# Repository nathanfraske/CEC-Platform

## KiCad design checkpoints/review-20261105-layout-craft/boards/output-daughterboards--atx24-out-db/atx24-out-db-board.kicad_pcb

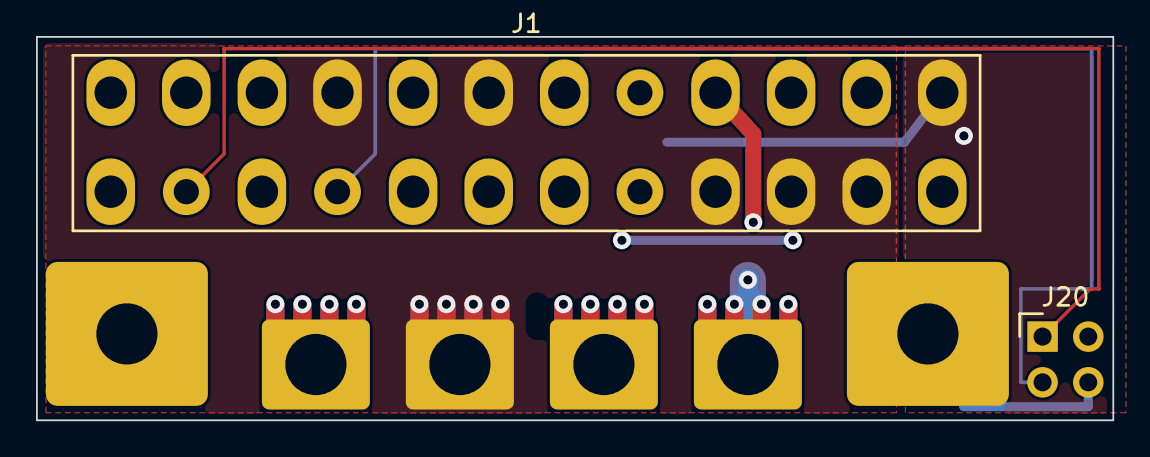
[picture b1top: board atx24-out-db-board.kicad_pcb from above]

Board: 4 copper layers, 59.8 x 21.3 mm, 8 parts (0 on the bottom side), 8 nets.

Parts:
J1: ATX24 OUT FIELD; ATX24_Daughterboard_Field_P4.20mm
J10, J11, J13, J15: T34069 DB M3 PAD; XFCN_T34069_Daughterboard_BoltPad_M3_PROVISIONAL
J16, J19: TTR32100127-0600 DB M3 PAD; XFCN_TTR32100127-0600_Daughterboard_BoltPad_M3_PROVISIONAL
J20: TSW-102-16-G-D-RA; Samtec_TSW-102-16-G-D-RA_2x02_P2.54mm_Horizontal

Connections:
+3V3: J1.1, J1.2, J1.12, J1.13, J13.1
+5V: J1.4, J1.6, J1.21, J1.22, J1.23, J11.1
+5VSB: J1.9, J15.1
+12V: J1.10, J1.11, J10.1
/-12V: J1.14, J20.1
/PS_ON#: J1.16, J20.2
/PWR_OK: J1.8, J20.3
GND: J1.3, J1.5, J1.7, J1.15, J1.17, J1.18, J1.19, J1.24, J16.1, J19.1, J20.4

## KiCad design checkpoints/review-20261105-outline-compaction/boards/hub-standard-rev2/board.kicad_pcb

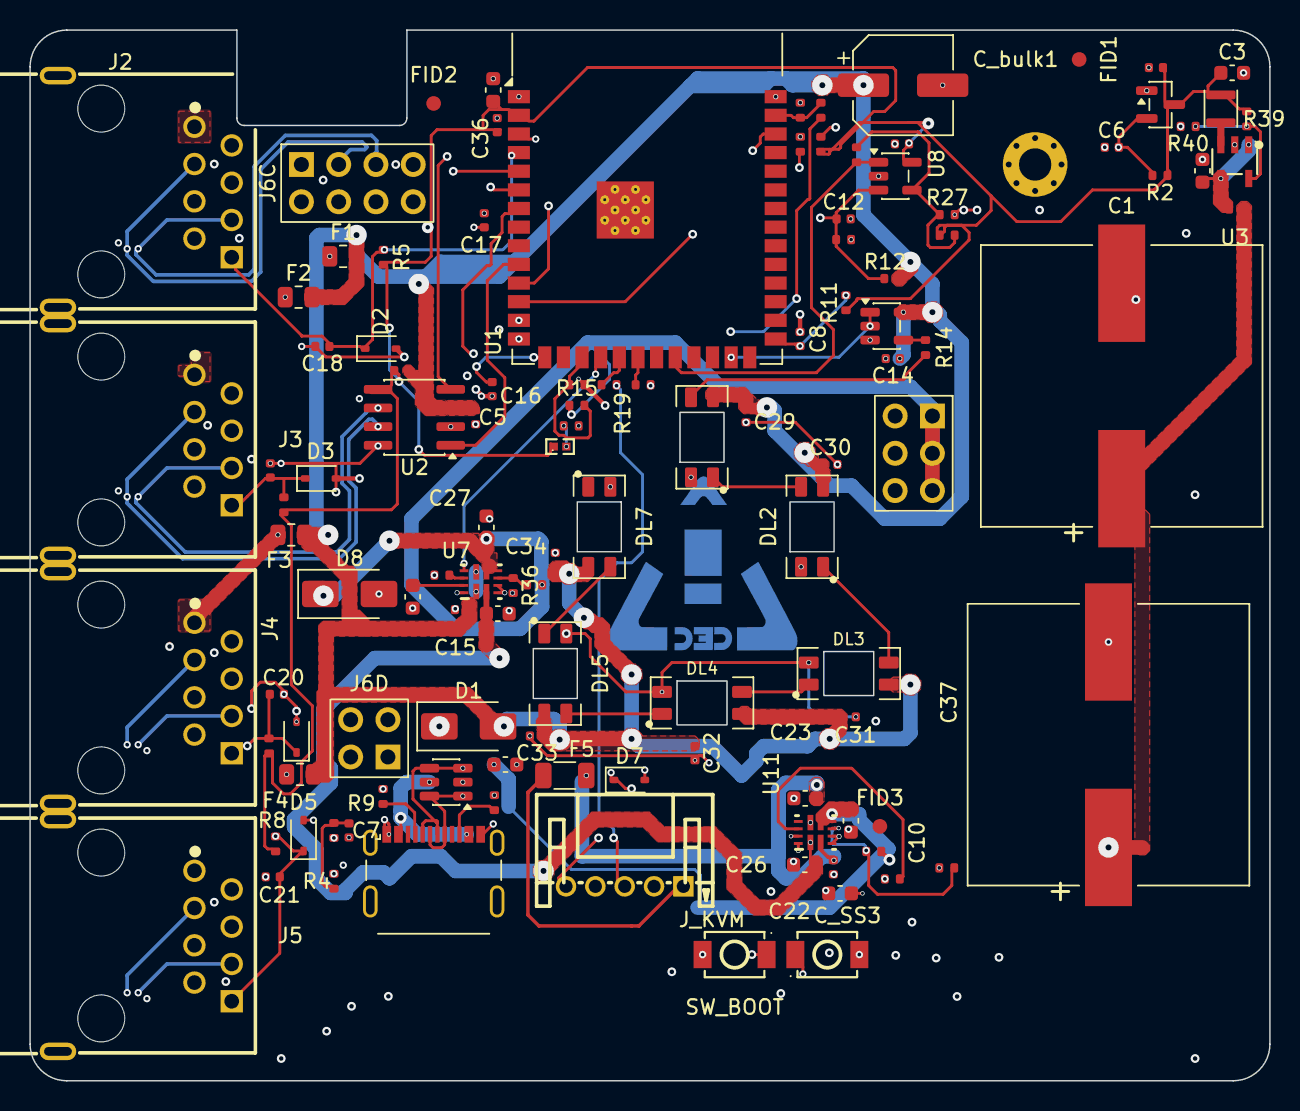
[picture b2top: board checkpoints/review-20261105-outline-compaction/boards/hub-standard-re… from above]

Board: 6 copper layers, 84.5 x 71.6 mm, 117 parts (1 on the bottom side), 58 nets.

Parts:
C1, C37: 4700uF; CP_Elec_Lelon_VZH_18x16.5
C2, C3, C23: 10uF; C_0603_1608Metric
C4, C5, C6, C8, C13, C14, C15, C16, C17, C18, C19, C20, C21, C22, C29, C30, C31, C32, C33, C34, C35, C36: 100nF; C_0402_1005Metric
C7: 4n7; C_0402_1005Metric
C10, C25, C26, C27, C28: 1uF; C_0603_1608Metric
C11: 22uF; C_0603_1608Metric
C12: 10nF; C_0402_1005Metric
C_SS2, C_SS3: 2.2uF; C_0603_1608Metric
C_bulk1: 470uF; CP_Elec_6.3x7.7
D1: SS14; D_SMA
D2, D3, D4, D5, D7: PESD5V0S1BA; D_SOD-323
D6: USBLC6-2SC6; SOT-23-6
D8: SMAJ5.0A; D_SMA
DL1, DL2, DL3, DL4, DL5, DL7: SK6812MINI-E; LED_SK6812MINI-E_3.2x2.8mm_P1.5mm_ReverseMount
F1, F2, F3, F4: PTC 500mA; R_0805_2012Metric
F5: 1.1A/16V PTC; R_1206_3216Metric
FID1, FID2, FID3: Fiducial_1mm_Mask2mm
H1: M2 GND lug; MountingHole_2.2mm_M2_Pad_Via_Slim_6mm_Hardware
J2: PORT1; RJ45_FTP_Shielded_Horizontal
J3: PORT2; RJ45_FTP_Shielded_Horizontal
J4: PORT3; RJ45_FTP_Shielded_Horizontal
J5: PORT4; RJ45_FTP_Shielded_Horizontal
J6C: TO-24PIN-STACK-COMMS; PinSocket_2x04_P2.54mm_Vertical
J6D: TO-24PIN-STACK-ID; PinSocket_2x02_P2.54mm_Vertical
J6P: TO-24PIN-STACK-PWR; PinSocket_2x03_P2.54mm_Vertical
J_KVM: CEC_NANOKVM_AUX_5P; JST_PH_S5B-PH-K-S_1x05_P2.00mm_Horizontal
J_USB: USB-C; USB_C_Receptacle_GCT_USB4215-03-A
L1: 2.2uH; VLS252010HBX-2R2M-1
LOGO1: CEC_Logo_Copper
R2, R5, R6, R7, R8, R11, R16, R22, R24, R25, R36, R38: 10kΩ; R_0402_1005Metric
R3, R4: 60.4; R_0402_1005Metric
R9, R10: 5.1kΩ; R_0402_1005Metric
R12, R15, R21, R23: 47kΩ; R_0402_1005Metric
R13: 27kΩ; R_0402_1005Metric
R14: 330Ω; R_0402_1005Metric
R19, R20: 33Ω; R_0402_1005Metric
R26: 11.0kOhm; R_0402_1005Metric
R27: 10.0kOhm; R_0402_1005Metric
R28: 1MOhm; R_0402_1005Metric
R35, R37: 43.2kΩ; R_0402_1005Metric
R39: 453kΩ; R_0402_1005Metric
R40: 100kΩ; R_0402_1005Metric
RJ_HOLD: 0R (jumper); R_0402_1005Metric
R_ILIM2, R_ILIM3: 27kΩ; R_0402_1005Metric
SW_BOOT: SW_BOOT; TS-1088-AR02016
SW_RESET: SW_RST; TS-1088-AR02016
TH1: NTC 10k; NTC_0402_1005Metric
U1: ESP32-S3-WROOM-1; ESP32-S3-WROOM-1_NoAntKeepout
U2: TJA1051T/3; SOIC-8_3.9x4.9mm_P1.27mm
U3: TLV62569DBVR; SOT-23-5_L3.0-W1.7-P0.95-LS2.8-BL
U4: TPS3839K33; SOT-23
U6: SN74AHCT1G08; SOT-23-5
U7, U11: TPS2121RUXR; RUX0012A
U8: TLV7011DBVR; SOT-23-5

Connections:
+3V3: C3.1, C4.1, C11.1, C13.1, C17.1, C35.1, C36.1, L1.2, R2.1, R5.1, R6.1, R7.1, R8.1, R11.1, R23.1, R26.1, R39.1, TH1.1, U1.2, U2.5, U4.3, U8.5
+5VSB: C5.1, C14.1, C15.1, C29.1, C30.1, C31.1, C32.1, C33.1, C34.1, C35.2, C_bulk1.1, D1.2, DL1.4, DL2.4, DL3.4, DL4.4, DL5.4, DL7.4, F1.2, F2.2, F3.2, F4.2, R12.1, U2.3, U6.5, U7.1, U7.8
+5V_SYS: C27.1, D8.1, J6P.1, J6P.3, J6P.5, R15.1, R35.1, U7.6, U7.7
/5V_SYS_SENSE: R15.2, R16.1, U1.17
/AUX_UART_RX: R20.1, U1.20
/AUX_UART_TX: R19.1, U1.19
/BLACKOUT_SENSE: C12.1, R12.2, R13.1, U1.12, U8.3
/CAN + FOUR MODULE PORTS + STACK/CAN_H: J2.3, J3.3, J4.3, J5.3, J6C.3, R3.1, U2.7
/CAN + FOUR MODULE PORTS + STACK/CAN_L: J2.6, J3.6, J4.6, J5.6, J6C.5, R4.2, U2.6
/CAN + FOUR MODULE PORTS + STACK/CAN_MID: C7.1, R3.2, R4.1
/CAN + FOUR MODULE PORTS + STACK/VCC_P1: F1.1, J2.1
/CAN + FOUR MODULE PORTS + STACK/VCC_P2: F2.1, J3.1
/CAN + FOUR MODULE PORTS + STACK/VCC_P3: F3.1, J4.1
/CAN + FOUR MODULE PORTS + STACK/VCC_P4: F4.1, J5.1
/CAN_RX: U1.11, U2.4
/CAN_TX: U1.10, U2.1
/DETECT1: C18.1, D2.1, J2.8, J6D.1, R5.2, U1.4
/DETECT2: C19.1, D3.1, J3.8, R6.2, U1.5
/DETECT3: C20.1, D4.1, J4.8, R7.2, U1.6
/DETECT4: C21.1, D5.1, J5.8, R8.2, U1.7
/HOLD-UP + 3V3 REGULATOR/+5V_HOLD: C1.1, C37.1, D1.1, RJ_HOLD.1
/HOLD-UP + 3V3 REGULATOR/BUCK_FB_3V3: R39.2, R40.1, U3.5
/HOLD-UP + 3V3 REGULATOR/BUCK_SW_3V3: L1.1, U3.3
/HOLD-UP + 3V3 REGULATOR/COMP_THRESH: R26.2, R27.1, R28.2, U8.4
/HOLD-UP + 3V3 REGULATOR/LOGIC_REG_IN: C2.1, RJ_HOLD.2, U3.1, U3.4
/HUB_3V3_SENSE: R23.2, R24.1, U1.38
/KVM AUXILIARY + RAIL SENSING/AUX_RXC: J_KVM.4, R20.2
/KVM AUXILIARY + RAIL SENSING/AUX_TXC: J_KVM.3, R19.2
/KVM AUXILIARY + RAIL SENSING/KVM_3V3_REF: D7.1, J_KVM.5, R21.1
/KVM AUXILIARY + RAIL SENSING/KVM_5V_RAW: F5.1, J_KVM.1
/KVM_3V3_SENSE: R21.2, R22.1, U1.39
/KVM_5V_IN: C22.1, C23.1, F5.2, U11.2
/LED_DATA: U1.25, U6.1, U6.2
/MCU + USB SERVICE PORT/EN: C6.2, R2.2, SW_RESET.2, U1.3, U4.2
/MCU + USB SERVICE PORT/GPIO0: C8.1, R11.2, SW_BOOT.2, U1.27
/MCU + USB SERVICE PORT/USB_CC1: J_USB.A5, R9.1
/MCU + USB SERVICE PORT/USB_CC2: J_USB.B5, R10.1
/MCU + USB SERVICE PORT/USB_D_N: D6.3, D6.4, J_USB.A7, J_USB.B7, U1.13
/MCU + USB SERVICE PORT/USB_D_P: D6.1, D6.6, J_USB.A6, J_USB.B6, U1.14
/POWER INPUT + SOURCE SELECTION/PSU_5V_KVM: C26.1, C28.1, U7.2, U11.1, U11.8
/POWER INPUT + SOURCE SELECTION/U7_ILM: R_ILIM2.1, U7.10
/POWER INPUT + SOURCE SELECTION/U7_OV1: R35.2, R36.1, U7.5
/POWER INPUT + SOURCE SELECTION/U7_SS: C_SS2.1, U7.11
/POWER INPUT + SOURCE SELECTION/U11_ILM: R_ILIM3.1, U11.10
/POWER INPUT + SOURCE SELECTION/U11_OV1: R37.2, R38.1, U11.5
/POWER INPUT + SOURCE SELECTION/U11_SS: C_SS3.2, U11.11
/PWR_FAIL_INT: R28.1, U1.22, U8.1
/PWR_SOURCE_STATUS: U1.18, U7.9
/STATUS LED CHAIN/Net-(U6-Y): R14.1, U6.4
/TEMP_HUB: C16.1, R25.1, TH1.2, U1.15
/USB_VBUS: C10.1, C25.1, D6.5, J_USB.A4, J_USB.A9, J_USB.B4, J_USB.B9, R37.1, U11.6, U11.7
GND: C1.2, C2.2, C3.2, C4.2, C5.2, C6.1, C7.2, C8.2, C10.2, C11.2, C12.2, C13.2, C14.2, C15.2, C16.2, C17.2, C18.2, C19.2, C20.2, C21.2, C22.2, C23.2, C25.2, C26.2, C27.2, C28.2, C29.2, C30.2, C31.2, C32.2, C33.2, C34.2, C36.2, C37.2, C_SS2.2, C_SS3.1, C_bulk1.2, D2.2, D3.2, D4.2, D5.2, D6.2, D7.2, D8.2, DL1.2, DL2.2, DL3.2, DL4.2, DL5.2, DL7.2, H1.1, J2.2, J2.SH1, J2.SH2, J3.2, J3.SH1, J3.SH2, J4.2, J4.SH1, J4.SH2, J5.2, J5.SH1, J5.SH2, J6C.1, J6C.2, J6C.7, J6C.8, J6D.2, J6D.4, J6P.2, J6P.4, J6P.6, J_KVM.2, J_USB.A1, J_USB.A12, J_USB.B1, J_USB.B12, J_USB.S1, R9.2, R10.2, R13.2, R16.2, R22.2, R24.2, R25.2, R27.2, R36.2, R38.2, R40.2, R_ILIM2.2, R_ILIM3.2, SW_BOOT.1, SW_RESET.1, U1.1, U1.40, U1.41, U2.2, U2.8, U3.2, U4.1, U6.3, U7.3, U7.4, U7.12, U8.2, U11.3, U11.4, U11.12
unnamed: DL1.3, R14.2
unnamed: DL1.1, DL2.3
unnamed: DL2.1, DL3.3
unnamed: DL3.1, DL4.3
unnamed: DL4.1, DL5.3
unnamed: DL5.1, DL7.3

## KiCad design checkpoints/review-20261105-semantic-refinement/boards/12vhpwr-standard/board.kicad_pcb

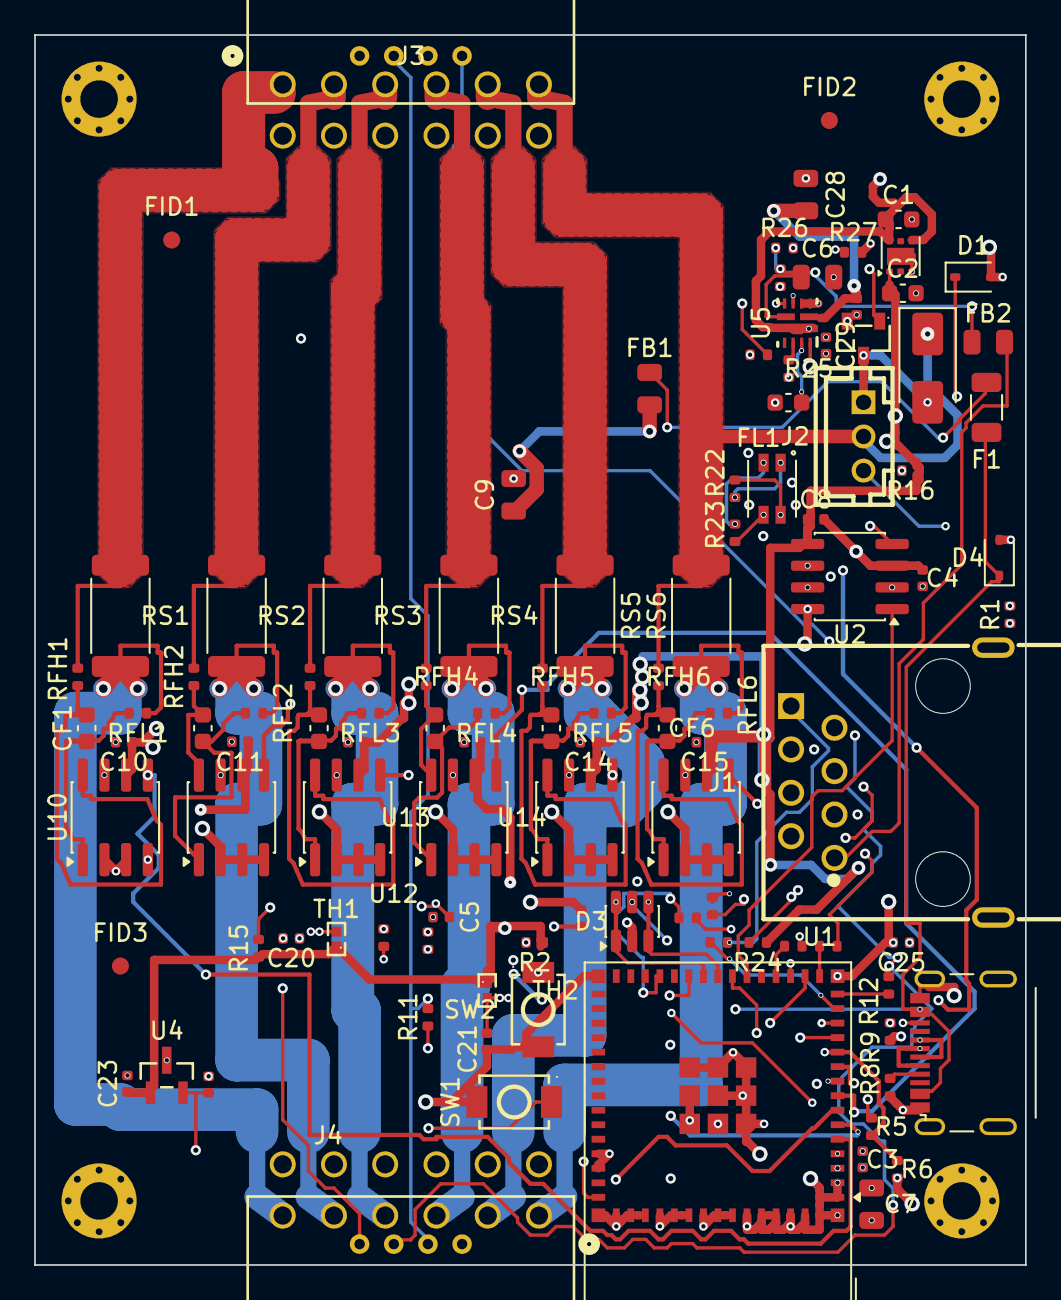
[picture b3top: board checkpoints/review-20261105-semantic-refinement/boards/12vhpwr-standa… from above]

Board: 6 copper layers, 58.0 x 72.0 mm, 110 parts (0 on the bottom side), 73 nets.

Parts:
C1: 10uF; C_0603_1608Metric
C2: 1uF; C_0603_1608Metric
C3, C4, C5, C8, C10, C11, C12, C13, C14, C15, C20, C21, C22, C23, C25, C27, C29: 100nF; C_0402_1005Metric
C6, C7, C9, C28: 10uF; C_0805_2012Metric
C24: 1nF; C_0402_1005Metric
C26: 2.2uF; C_0603_1608Metric
CF1, CF2, CF3, CF4, CF5, CF6: 470nF; C_0603_1608Metric
D1, D4: PESD5V0S1BA; D_SOD-323
D3: USBLC6-2SC6; SOT-23-6
D5: SS34; D_SMA
F1: 750mA/16V PTC; R_1206_3216Metric
FB1: MPZ2012S601AT000; C_0805_2012Metric
FB2: 0R; C_0805_2012Metric
FID1, FID2, FID3: Fiducial_1mm_Mask2mm
FL1: ACT1210L-101-2P-TL00 (DNP); TDK_ACT1210L_CEC_13_24
H1, H2, H3, H4: M2_PTH_GND_Slim_6mm_Hardware; MountingHole_2.2mm_M2_Pad_Via_Slim_6mm_Hardware
J1: TO-HUB; RJ45_FTP_Shielded_Horizontal
J2: CEC_FAN_3P; JST_PH_B3B-PH-K-S_1x03_P2.00mm_Vertical
J3: 12V-2x6 IN; CEC_12V2x6_Horizontal
J4: 12V-2x6 OUT pigtail; CEC_12V2x6_Horizontal
J5: USB-C 2.0; USB_C_Receptacle_GCT_USB4215-03-A
Q1: AO3400A; SOT-23-3_L2.9-W1.3-P1.90-LS2.4-BR
R1: 2.2kΩ; R_0402_1005Metric
R2, R6, R15, R16, R20, R21, R24, R27: 10kΩ; R_0402_1005Metric
R5: 47kΩ; R_0402_1005Metric
R7, R25, R28: 100kΩ; R_0402_1005Metric
R8, R9: 5.1kΩ; R_0402_1005Metric
R10, R11, R12, R13, R17: 1kΩ; R_0402_1005Metric
R14: 100Ω; R_0402_1005Metric
R22, R23: 0Ω; R_0402_1005Metric
R26: 43.2kΩ; R_0402_1005Metric
R29: 33kΩ; R_0402_1005Metric
RFH1, RFH2, RFH3, RFH4, RFH5, RFH6: 10Ω; R_0402_1005Metric
RFL1, RFL2, RFL3, RFL4, RFL5, RFL6: 10Ω; R_0402_1005Metric
RS1, RS2, RS3, RS4, RS5, RS6: 1mΩ; R_2512_6332Metric
SW1: BOOT; TS-1088-AR02016
SW2: RESET; TS-1088-AR02016
TH1, TH2: NTC 10k; NTC_0402_1005Metric
U1: ESP32-S3-MINI-1-N4R2; ESP32-S2-MINI-1_NoAntKeepout
U2: TJA1051T/3; SOIC-8_3.9x4.9mm_P1.27mm
U4: REF3030; REF3030_DBZ3
U5: TPS2121RUXR; RUX0012A
U10, U11, U12, U13, U14, U15: INA240A3; SOIC-8_3.9x4.9mm_P1.27mm
U16: TLV75533PDRVR; WSON-6-1EP_2x2mm_P0.65mm_EP1x1.6mm

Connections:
+3V3: C2.1, C3.1, C7.1, C8.1, C10.1, C11.1, C12.1, C13.1, C14.1, C15.1, C23.1, R2.1, R15.1, R16.1, R24.1, TH1.1, TH2.1, U1.3, U2.5, U4.1, U10.6, U11.6, U12.6, U13.6, U14.6, U15.6, U16.1
+5VSB: C1.1, C4.1, C8.2, C29.1, U2.3, U5.1, U5.8, U16.4, U16.6
/01-input/FAN_GATE: Q1.1, R14.2, R15.2
/01-input/FAN_RET: D5.2, J2.1, Q1.3
/01-input/FAN_TACH: J2.3, R16.2, R17.1
/08-usb/U5_ILM: R25.1, U5.10
/08-usb/U5_OV1: R26.2, R27.1, U5.5
/08-usb/U5_PR1: R28.2, R29.1, U5.6
/08-usb/U5_SS: C26.1, U5.11
/CAN_H: FL1.1, J1.3, R22.1
/CAN_H_INT: FL1.3, R22.2, U2.7
/CAN_L: FL1.2, J1.6, R23.1
/CAN_L_INT: FL1.4, R23.2, U2.6
/CAN_RX: U1.22, U2.4
/CAN_TX: U1.21, U2.1
/DETECT: D1.1, J1.8, R1.1, R7.1
/DETECT_SENSE: R7.2, U1.14
/EN: C5.1, R2.2, SW2.2, U1.45
/FAN_12V: D5.1, J2.2, J3.6, R5.1, RFH6.1, RS6.1
/FAN_EN: R14.1, U1.25
/FAN_TACH_GPIO: R17.2, U1.27
/GPIO0: C25.1, R24.2, SW1.2, U1.4
/IN1_N: CF1.2, RFL1.2, U10.1
/IN1_P: CF1.1, RFH1.2, U10.8
/IN2_N: CF2.2, RFL2.2, U11.1
/IN2_P: CF2.1, RFH2.2, U11.8
/IN3_N: CF3.2, RFL3.2, U12.1
/IN3_P: CF3.1, RFH3.2, U12.8
/IN4_N: CF4.2, RFL4.2, U13.1
/IN4_P: CF4.1, RFH4.2, U13.8
/IN5_N: CF5.2, RFL5.2, U14.1
/IN5_P: CF5.1, RFH5.2, U14.8
/IN6_N: CF6.2, RFL6.2, U15.1
/IN6_P: CF6.1, RFH6.2, U15.8
/ISENSEP1: U1.5, U10.5
/ISENSEP2: U1.6, U11.5
/ISENSEP3: U1.7, U12.5
/ISENSEP4: U1.8, U13.5
/ISENSEP5: U1.9, U14.5
/ISENSEP6: U1.10, U15.5
/SB_CBL_PRES: J3.16, J4.16, R13.1
/SB_CBL_PRES_GPIO: R13.2, U1.16
/SB_PWR_STABLE: J3.15, J4.15, R12.1
/SB_PWR_STABLE_GPIO: R12.2, U1.15
/SB_SENSE0: J3.13, J4.13, R10.1
/SB_SENSE0_GPIO: R10.2, U1.19
/SB_SENSE1: J3.14, J4.14, R11.1
/SB_SENSE1_GPIO: R11.2, U1.13
/SENSEP1_HI: J3.1, RFH1.1, RS1.1
/SENSEP1_LO: J4.6, RFL1.1, RS1.2
/SENSEP2_HI: J3.2, RFH2.1, RS2.1
/SENSEP2_LO: J4.5, RFL2.1, RS2.2
/SENSEP3_HI: J3.3, RFH3.1, RS3.1
/SENSEP3_LO: J4.4, RFL3.1, RS3.2
/SENSEP4_HI: J3.4, RFH4.1, RS4.1
/SENSEP4_LO: J4.3, RFL4.1, RS4.2
/SENSEP5_HI: J3.5, RFH5.1, RS5.1
/SENSEP5_LO: J4.2, RFL5.1, RS5.2
/SENSEP6_LO: J4.1, RFL6.1, RS6.2
/TEMP1: C20.1, R20.1, TH1.2, U1.17
/TEMP2: C21.1, R21.1, TH2.2, U1.18
/USB_CC1: J5.A5, R8.1
/USB_CC2: J5.B5, R9.1
/USB_DM: D3.3, D3.4, J5.A7, J5.B7, U1.23
/USB_DP: D3.1, D3.6, J5.A6, J5.B6, U1.24
/VBUS: C9.1, C27.1, C28.1, FB1.2, U5.2
/VBUS_F: F1.2, FB1.1
/VBUS_RAW: D3.5, D4.1, F1.1, J5.A4, J5.A9, J5.B4, J5.B9
/VCC_RAW: FB2.2, J1.1
/VCC_RJ45: C6.1, FB2.1, R26.1, R28.1, U5.7
/VRAIL_DIV: C24.1, R5.2, R6.1, U1.11
/VREF: C22.1, U1.12, U4.2
GND: C1.2, C2.2, C3.2, C4.2, C5.2, C6.2, C7.2, C9.2, C10.2, C11.2, C12.2, C13.2, C14.2, C15.2, C20.2, C21.2, C22.2, C23.2, C24.2, C25.2, C26.2, C27.2, C28.2, C29.2, D1.2, D3.2, D4.2, H1.1, H2.1, H3.1, H4.1, J1.2, J1.SH1, J1.SH2, J3.7, J3.8, J3.9, J3.10, J3.11, J3.12, J4.7, J4.8, J4.9, J4.10, J4.11, J4.12, J5.A1, J5.A12, J5.B1, J5.B12, J5.S1, Q1.2, R1.2, R6.2, R8.2, R9.2, R20.2, R21.2, R25.2, R27.2, R29.2, SW1.1, SW2.1, U1.1, U1.2, U1.42, U1.43, U1.46, U1.47, U1.48, U1.49, U1.50, U1.51, U1.52, U1.53, U1.54, U1.55, U1.56, U1.57, U1.58, U1.59, U1.60, U1.61, U1.62, U1.63, U1.64, U1.65, U2.2, U2.8, U4.3, U5.3, U5.4, U5.12, U10.2, U10.3, U10.4, U10.7, U11.2, U11.3, U11.4, U11.7, U12.2, U12.3, U12.4, U12.7, U13.2, U13.3, U13.4, U13.7, U14.2, U14.3, U14.4, U14.7, U15.2, U15.3, U15.4, U15.7, U16.3, U16.7

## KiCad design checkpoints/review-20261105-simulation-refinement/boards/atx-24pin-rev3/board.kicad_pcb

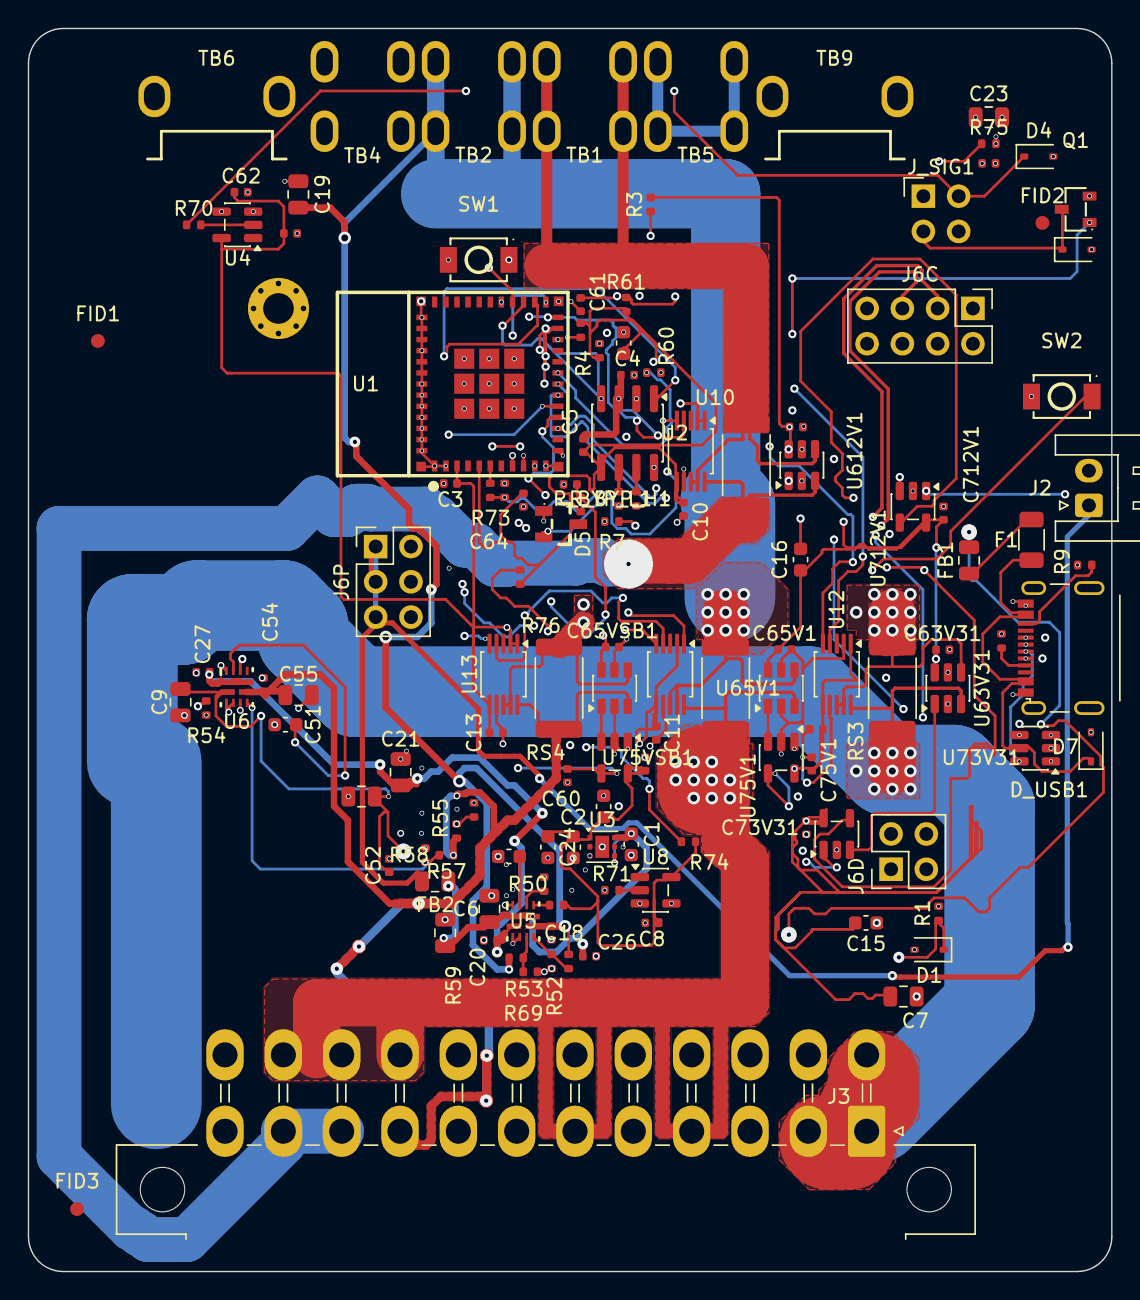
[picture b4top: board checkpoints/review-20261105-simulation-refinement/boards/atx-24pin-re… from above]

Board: 6 copper layers, 78.0 x 89.5 mm, 129 parts (0 on the bottom side), 63 nets.

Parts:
C1, C2, C14, C15, C16, C17, C24: 1uF; C_0603_1608Metric
C3, C4, C5, C8, C10, C11, C12, C13, C18, C20, C22, C26, C27, C28, C52, C54, C60, C61, C62, C63, C63V31, C64, C65V1, C65VSB1, C73V31, C75V1, C75VSB1, C612V1, C712V1: 100nF; C_0402_1005Metric
C6, C7, C9, C19, C21, C23, C53, C55: 10uF; C_0805_2012Metric
C25: 22uF; C_0805_2012Metric
C50: 2u2; C_0603_1608Metric
C51: 2.2uF; C_0603_1608Metric
D1, D3, D4, D7: PESD5V0S1BA; D_SOD-323
D5: BAT54S; SOT-23-3_L2.9-W1.3-P1.90-LS2.4-TL
D_USB1: USBLC6-2SC6; SOT-23-6
F1: 750mA/16V PTC; R_1206_3216Metric
FB1: 600R@100MHz FB (MPZ2012S601AT000); C_0805_2012Metric
FB2: 0R (FB position, populate on EMC evidence); C_0805_2012Metric
FID1, FID2, FID3: Fiducial_1mm_Mask2mm
H1: M2 GND lug; MountingHole_2.2mm_M2_Pad_Via_Slim_6mm_Hardware
J2: TO-HUB-PWR; JST_XH_S2B-XH-A_1x02_P2.50mm_Horizontal
J3: ATX-24 PSU; Molex_Mini-Fit_Jr_5569-24A1_2x12_P4.20mm_Horizontal
J5: USB-C 2.0; USB_C_Receptacle_GCT_USB4215-03-A
J6C: TO-HUB-STACK-COMMS; PinHeader_2x04_P2.54mm_Vertical
J6D: TO-HUB-STACK-ID; PinHeader_2x02_P2.54mm_Vertical
J6P: TO-HUB-STACK-PWR; PinHeader_2x03_P2.54mm_Vertical
J_SIG1: SSQ-102-03-G-D; Samtec_SSQ-102-03-G-D_2x02_P2.54mm_Vertical
Q1: AO3400A; SOT-23-3_L2.9-W1.3-P1.90-LS2.4-BR
R1, R3, R4: 2.2kΩ; R_0402_1005Metric
R2, R10, R51, R56, R60, R61, R69, R76: 10kΩ; R_0402_1005Metric
R7, R52, R54, R57, R73, R75: 100kΩ; R_0402_1005Metric
R8, R9: 5.1kΩ; R_0402_1005Metric
R50: 20kΩ; R_0402_1005Metric
R53, R58: 33kΩ; R_0402_1005Metric
R55, R59: 43.2kΩ; R_0402_1005Metric
R70, R71: 1kΩ; R_0402_1005Metric
R72: 100Ω; R_0402_1005Metric
R74: 15kΩ; R_0402_1005Metric
RS1, RS2, RS3: 2mΩ; R_2512_6332Metric
RS4: R025; R_2512_6332Metric
R_BYP_H1: 0Ω; R_0402_1005Metric
R_BYP_L1: 0Ω; R_0402_1005Metric
SW1: BOOT; TS-1088-AR02016
SW2: RESET; TS-1088-AR02016
TB1, TB2, TB4, TB5: XFCN T34069; XFCN_T34069_THT_M3_40A
TB6, TB9: TTR32100127-0600; XFCN_TTR32100127-0600_THT_M3_60A
U1: ESP32-C6-MINI-1-N4; ESP32-C6-MINI-1
U2: TJA1051T/3; SOIC-8_3.9x4.9mm_P1.27mm
U3: TLV75533PDRVR; WSON-6-1EP_2x2mm_P0.65mm_EP1x1.6mm
U4, U8: 74LVC1G17; SOT-23-5
U5, U6: TPS2121RUXR; RUX0012A
U10, U11, U12, U13: INA238; VSSOP-10_3x3mm_P0.5mm
U63V31, U612V1: INA181A2IDBVR; SOT-23-6
U65V1, U65VSB1: INA181A2IDBVR; SOT-23-6_TI_DBV0006A
U73V31, U75V1, U75VSB1, U712V1: TLV7011DBVR; SOT-23-5

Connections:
+3V3: C2.1, C3.1, C7.1, C8.1, C10.1, C11.1, C12.1, C13.1, C14.1, C15.1, C16.1, C17.1, C24.1, C28.1, C62.1, C63.1, C63V31.1, C65V1.1, C65VSB1.1, C73V31.1, C75V1.1, C75VSB1.1, C612V1.1, C712V1.1, D5.2, R2.1, R3.2, R4.2, R10.1, R51.2, R61.1, R74.1, U1.3, U2.5, U3.1, U4.5, U8.5, U10.6, U11.2, U11.6, U12.1, U12.6, U13.1, U13.2, U13.6, U63V31.6, U65V1.6, U65VSB1.6, U73V31.5, U75V1.5, U75VSB1.5, U612V1.6, U712V1.5
+5VSB: C54.1, C55.1, J3.9, R55.1, R57.1, RS4.1, U6.7, U13.10, U65VSB1.3
+5V_MAIN: C18.1, C19.1, R52.1, R59.1, RS2.2, TB2.1, U5.7, U11.8, U11.9, U65V1.4
+5V_SYS: C1.1, C4.1, C6.1, C25.1, C26.1, C28.2, FB2.1, U2.3, U3.4, U3.6, U5.1, U5.8
/3V3 REGULATOR + MCU/EN: C5.1, R2.2, SW2.2, U1.8
/3V3 REGULATOR + MCU/IO8_STRAP: R10.2, U1.22
/5V SOURCE MUX + USB SERVICE INGRESS/5VSB_MUX: C20.1, C21.1, C27.1, U5.2, U6.1, U6.8
/5V SOURCE MUX + USB SERVICE INGRESS/ILIM: R50.1, U5.10
/5V SOURCE MUX + USB SERVICE INGRESS/MUX_ST: R51.1, U5.9
/5V SOURCE MUX + USB SERVICE INGRESS/PR1: R52.2, R53.1, U5.6
/5V SOURCE MUX + USB SERVICE INGRESS/SS: C50.1, U5.11
/5V SOURCE MUX + USB SERVICE INGRESS/U5_OV1: R59.2, R69.1, U5.5
/5V SOURCE MUX + USB SERVICE INGRESS/U6_ILM: R54.1, U6.10
/5V SOURCE MUX + USB SERVICE INGRESS/U6_OV1: R55.2, R56.1, U6.5
/5V SOURCE MUX + USB SERVICE INGRESS/U6_PR1: R57.2, R58.1, U6.6
/5V SOURCE MUX + USB SERVICE INGRESS/U6_SS: C51.1, U6.11
/5V SOURCE MUX + USB SERVICE INGRESS/USB_CC1: J5.A5, R8.1
/5V SOURCE MUX + USB SERVICE INGRESS/USB_CC2: J5.B5, R9.1
/5V SOURCE MUX + USB SERVICE INGRESS/VBUS: C9.1, C52.1, C53.1, FB1.2, U6.2
/5V SOURCE MUX + USB SERVICE INGRESS/VBUS_F: F1.2, FB1.1
/5V SOURCE MUX + USB SERVICE INGRESS/VBUS_RAW: D7.1, D_USB1.5, F1.1, J5.A4, J5.A9, J5.B4, J5.B9
/ATX INTERPOSER + CONTROL SIGNALS/ATX_NEG12V: C22.1, C23.1, J3.14, J_SIG1.1, R75.2
/ATX INTERPOSER + CONTROL SIGNALS/ATX_PSON: D3.1, J3.16, J_SIG1.2, Q1.3, R71.1
/ATX INTERPOSER + CONTROL SIGNALS/ATX_PWROK: D4.1, J3.8, J_SIG1.3, R70.1
/ATX INTERPOSER + CONTROL SIGNALS/NEG12V_DIV: R74.2, R75.1, R76.1
/ATX INTERPOSER + CONTROL SIGNALS/PSON_BUF: R71.2, U8.2
/ATX INTERPOSER + CONTROL SIGNALS/PSON_GATE: Q1.1, R72.2, R73.1
/ATX INTERPOSER + CONTROL SIGNALS/PWROK_BUF: R70.2, U4.2
/CAN_RX: U1.27, U2.4
/CAN_TX: U1.26, U2.1
/DET3V3: U1.15, U73V31.1
/DET5V: U1.29, U75V1.1
/DET5VSB: U1.16, U75VSB1.1
/DET12V: U1.28, U712V1.1
/DETECT_SENSE: R7.1, U1.12
/FOUR-RAIL PRECISION + FAST SENSING/DETAMP3V3: U63V31.1, U73V31.3
/FOUR-RAIL PRECISION + FAST SENSING/DETAMP5V: U65V1.1, U75V1.3
/FOUR-RAIL PRECISION + FAST SENSING/DETAMP5VSB: U65VSB1.1, U75VSB1.3
/FOUR-RAIL PRECISION + FAST SENSING/DETAMP12V: U612V1.1, U712V1.3
/FOUR-RAIL PRECISION + FAST SENSING/THRESH: C60.1, R60.2, U73V31.4, U75V1.4, U75VSB1.4, U712V1.4
/GPIO0: C61.1, R61.2, SW1.2, U1.23
/HUB LINK + CAN + STACK/+5V_SYS_PORT: FB2.2, J2.1, J6P.1, J6P.3, J6P.5
/HUB LINK + CAN + STACK/CAN_H: R_BYP_H1.2, U2.7
/HUB LINK + CAN + STACK/CAN_H_BUS: J6C.3, R_BYP_H1.1
/HUB LINK + CAN + STACK/CAN_L: R_BYP_L1.2, U2.6
/HUB LINK + CAN + STACK/CAN_L_BUS: J6C.5, R_BYP_L1.1
/HUB LINK + CAN + STACK/DETECT: D1.1, J6D.1, R1.1, R7.2
/I2C_SCL: R4.1, U1.25, U10.5, U11.5, U12.5, U13.5
/I2C_SDA: R3.1, U1.24, U10.4, U11.4, U12.4, U13.4
/NEG12V_ADC: C64.1, D5.3, R76.2, U1.5
/PSON_DRIVE: R72.1, U1.6
/PSON_SENSE: U1.10, U8.4
/PWROK_SENSE: U1.9, U4.4
/SENSE3V3_HI: J3.1, J3.2, J3.12, J3.13, RS3.1, U12.10, U63V31.3
/SENSE3V3_LO: RS3.2, TB4.1, U12.8, U12.9, U63V31.4
/SENSE5VSB_LO: RS4.2, TB5.1, U13.8, U13.9, U65VSB1.4
/SENSE5V_HI: J3.4, J3.6, J3.21, J3.22, J3.23, RS2.1, U11.10, U65V1.3
/SENSE12V_HI: J3.10, J3.11, RS1.1, U10.10, U612V1.3
/SENSE12V_LO: RS1.2, TB1.1, U10.8, U10.9, U612V1.4
/THRESH_PWM: R60.1, U1.19
/USB_D_N: D_USB1.3, D_USB1.4, J5.A7, J5.B7, U1.17
/USB_D_P: D_USB1.1, D_USB1.6, J5.A6, J5.B6, U1.18
GND: C1.2, C2.2, C3.2, C4.2, C5.2, C6.2, C7.2, C8.2, C9.2, C10.2, C11.2, C12.2, C13.2, C14.2, C15.2, C16.2, C17.2, C18.2, C19.2, C20.2, C21.2, C22.2, C23.2, C24.2, C25.2, C26.2, C27.2, C50.2, C51.2, C52.2, C53.2, C54.2, C55.2, C60.2, C61.2, C62.2, C63.2, C63V31.2, C64.2, C65V1.2, C65VSB1.2, C73V31.2, C75V1.2, C75VSB1.2, C612V1.2, C712V1.2, D1.2, D3.2, D4.2, D5.1, D7.2, D_USB1.2, H1.1, J2.2, J3.3, J3.5, J3.7, J3.15, J3.17, J3.18, J3.19, J3.24, J5.A1, J5.A12, J5.B1, J5.B12, J5.S1, J6C.1, J6C.2, J6C.7, J6C.8, J6D.2, J6D.4, J6P.2, J6P.4, J6P.6, J_SIG1.4, Q1.2, R1.2, R8.2, R9.2, R50.2, R53.2, R54.2, R56.2, R58.2, R69.2, R73.2, SW1.1, SW2.1, TB6.1, TB9.1, U1.1, U1.2, U1.11, U1.14, U1.36, U1.37, U1.38, U1.39, U1.40, U1.41, U1.42, U1.43, U1.44, U1.45, U1.46, U1.47, U1.48, U1.49, U1.50, U1.51, U1.52, U1.53, U2.2, U2.8, U3.3, U3.7, U4.3, U5.3, U5.4, U5.12, U6.3, U6.4, U6.12, U8.3, U10.1, U10.2, U10.7, U11.1, U11.7, U12.2, U12.7, U13.7, U63V31.2, U63V31.5, U65V1.2, U65V1.5, U65VSB1.2, U65VSB1.5, U73V31.2, U75V1.2, U75VSB1.2, U612V1.2, U612V1.5, U712V1.2

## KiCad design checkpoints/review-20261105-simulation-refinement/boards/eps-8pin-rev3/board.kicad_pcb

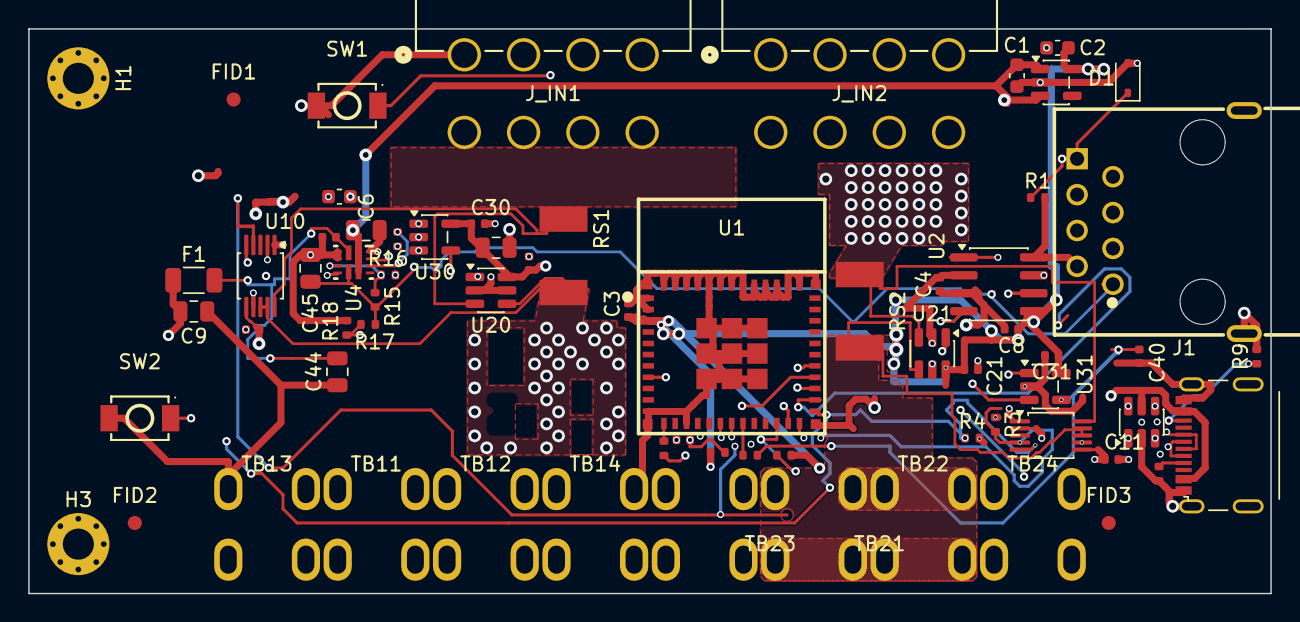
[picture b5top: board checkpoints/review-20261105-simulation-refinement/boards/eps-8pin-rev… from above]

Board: 6 copper layers, 88.0 x 40.0 mm, 68 parts (0 on the bottom side), 35 nets.

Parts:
C1, C2: 1uF; C_0603_1608Metric
C3, C4, C5, C8, C10, C11, C20, C21, C30, C31, C40, C43: 100nF; C_0402_1005Metric
C6, C9, C44, C45: 10uF; C_0805_2012Metric
C7: 4.7uF; C_0805_2012Metric
C42: 2.2uF; C_0603_1608Metric
D1: PESD5V0S1BA; D_SOD-323
D3: USBLC6-2SC6; SOT-23-6
F1: 750mA/16V PTC; R_1206_3216Metric
FID1, FID2, FID3: Fiducial_1mm_Mask2mm
H1, H3: MountingHole_2.2mm_M2_Pad_Via
J1: TO-HUB; RJ45_FTP_Shielded_Horizontal
J5: USB-C 2.0; USB_C_Receptacle_GCT_USB4215-03-A
J_IN1: C1 PSU; Molex_Mini-Fit_Jr_87427-0802_2x04_P4.20mm_RA
J_IN2: C2 PSU; Molex_Mini-Fit_Jr_87427-0802_2x04_P4.20mm_RA
R1, R3, R4: 2.2kΩ; R_0402_1005Metric
R2, R10, R19: 10kΩ; R_0402_1005Metric
R7: 100kΩ; R_0402_1005Metric
R8, R9: 5.1kΩ; R_0402_1005Metric
R14, R17: 100kOhm; R_0402_1005Metric
R15: 43.2kOhm; R_0402_1005Metric
R16: 10kOhm; R_0402_1005Metric
R18: 33kOhm; R_0402_1005Metric
RS1, RS2: 0.5mΩ; R_Bourns_CSS2H-2512R_L500
SW1: BOOT; TS-1088-AR02016
SW2: RESET; TS-1088-AR02016
TB11, TB12, TB13, TB14, TB21, TB22, TB23, TB24: XFCN T34069; XFCN_T34069_THT_M3_40A
U1: ESP32-C6-MINI-1-N4; ESP32-C6-MINI-1
U2: TJA1051T/3; SOIC-8_3.9x4.9mm_P1.27mm
U3: LP5907MFX-3.3; SOT-23-5
U4: TPS2121RUXR; RUX0012A
U10, U11: INA238; VSSOP-10_3x3mm_P0.5mm
U20, U21: INA181A2IDBVR; SOT-23-6
U30, U31: TLV7011DBVR; SOT-23-5

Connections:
+3V3: C2.1, C3.1, C7.1, C8.1, C10.1, C11.1, C20.1, C21.1, C30.1, C31.1, R2.1, R3.2, R4.2, R19.1, U1.3, U2.5, U3.5, U10.6, U11.2, U11.6, U20.6, U21.6, U30.5, U31.5
+5VSB: C1.1, C4.1, C6.1, C8.2, U2.3, U3.1, U3.3, U4.1, U4.8
/CAN_H: J1.3, U2.7
/CAN_L: J1.6, U2.6
/CAN_RX: U1.27, U2.4
/CAN_TX: U1.26, U2.1
/DETAMPC1: U20.1, U30.3
/DETAMPC2: U21.1, U31.3
/DETC1: U1.28, U30.1
/DETC2: U1.29, U31.1
/DETECT: D1.1, J1.8, R1.1, R7.1
/DETECT_SENSE: R7.2, U1.12
/EN: C5.1, R2.2, SW2.2, U1.8
/GPIO0: SW1.2, U1.23
/I2C_SCL: R4.1, U1.25, U10.5, U11.5
/I2C_SDA: R3.1, U1.24, U10.4, U11.4
/IO8_STRAP: R19.2, U1.22
/SENSEC1_HI: J_IN1.5, J_IN1.6, J_IN1.7, J_IN1.8, RS1.1, U10.10, U20.3
/SENSEC1_LO: RS1.2, TB11.1, TB12.1, U10.8, U10.9, U20.4
/SENSEC2_HI: J_IN2.5, J_IN2.6, J_IN2.7, J_IN2.8, RS2.1, U11.10, U21.3
/SENSEC2_LO: RS2.2, TB21.1, TB22.1, U11.8, U11.9, U21.4
/THRESH: C40.1, R10.2, U30.4, U31.4
/THRESH_PWM: R10.1, U1.19
/USB-C SERVICE INGRESS/U4_ILIM: R14.1, U4.10
/USB-C SERVICE INGRESS/U4_OV1: R15.2, R16.1, U4.5
/USB-C SERVICE INGRESS/U4_PR1: R17.2, R18.1, U4.6
/USB-C SERVICE INGRESS/U4_SS: C42.1, U4.11
/USB-C SERVICE INGRESS/VBUS_FUSED: C43.1, C44.1, F1.2, U4.2
/USB_CC1: J5.A5, R8.1
/USB_CC2: J5.B5, R9.1
/USB_D_N: D3.3, D3.4, J5.A7, J5.B7, U1.17
/USB_D_P: D3.1, D3.6, J5.A6, J5.B6, U1.18
/VBUS: C9.1, D3.5, F1.1, J5.A4, J5.A9, J5.B4, J5.B9
GND: C1.2, C2.2, C3.2, C4.2, C5.2, C6.2, C7.2, C9.2, C10.2, C11.2, C20.2, C21.2, C30.2, C31.2, C40.2, C42.2, C43.2, C44.2, C45.2, D1.2, D3.2, J1.2, J1.SH1, J1.SH2, J5.A1, J5.A12, J5.B1, J5.B12, J5.S1, J_IN1.1, J_IN1.2, J_IN1.3, J_IN1.4, J_IN2.1, J_IN2.2, J_IN2.3, J_IN2.4, R1.2, R8.2, R9.2, R14.2, R16.2, R18.2, SW1.1, SW2.1, TB13.1, TB14.1, TB23.1, TB24.1, U1.1, U1.2, U1.11, U1.14, U1.36, U1.37, U1.38, U1.39, U1.40, U1.41, U1.42, U1.43, U1.44, U1.45, U1.46, U1.47, U1.48, U1.49, U1.50, U1.51, U1.52, U1.53, U2.2, U2.8, U3.2, U4.3, U4.4, U4.12, U10.1, U10.2, U10.7, U11.1, U11.7, U20.2, U20.5, U21.2, U21.5, U30.2, U31.2
VCC_RJ45: C45.1, J1.1, R15.1, R17.1, U4.7
